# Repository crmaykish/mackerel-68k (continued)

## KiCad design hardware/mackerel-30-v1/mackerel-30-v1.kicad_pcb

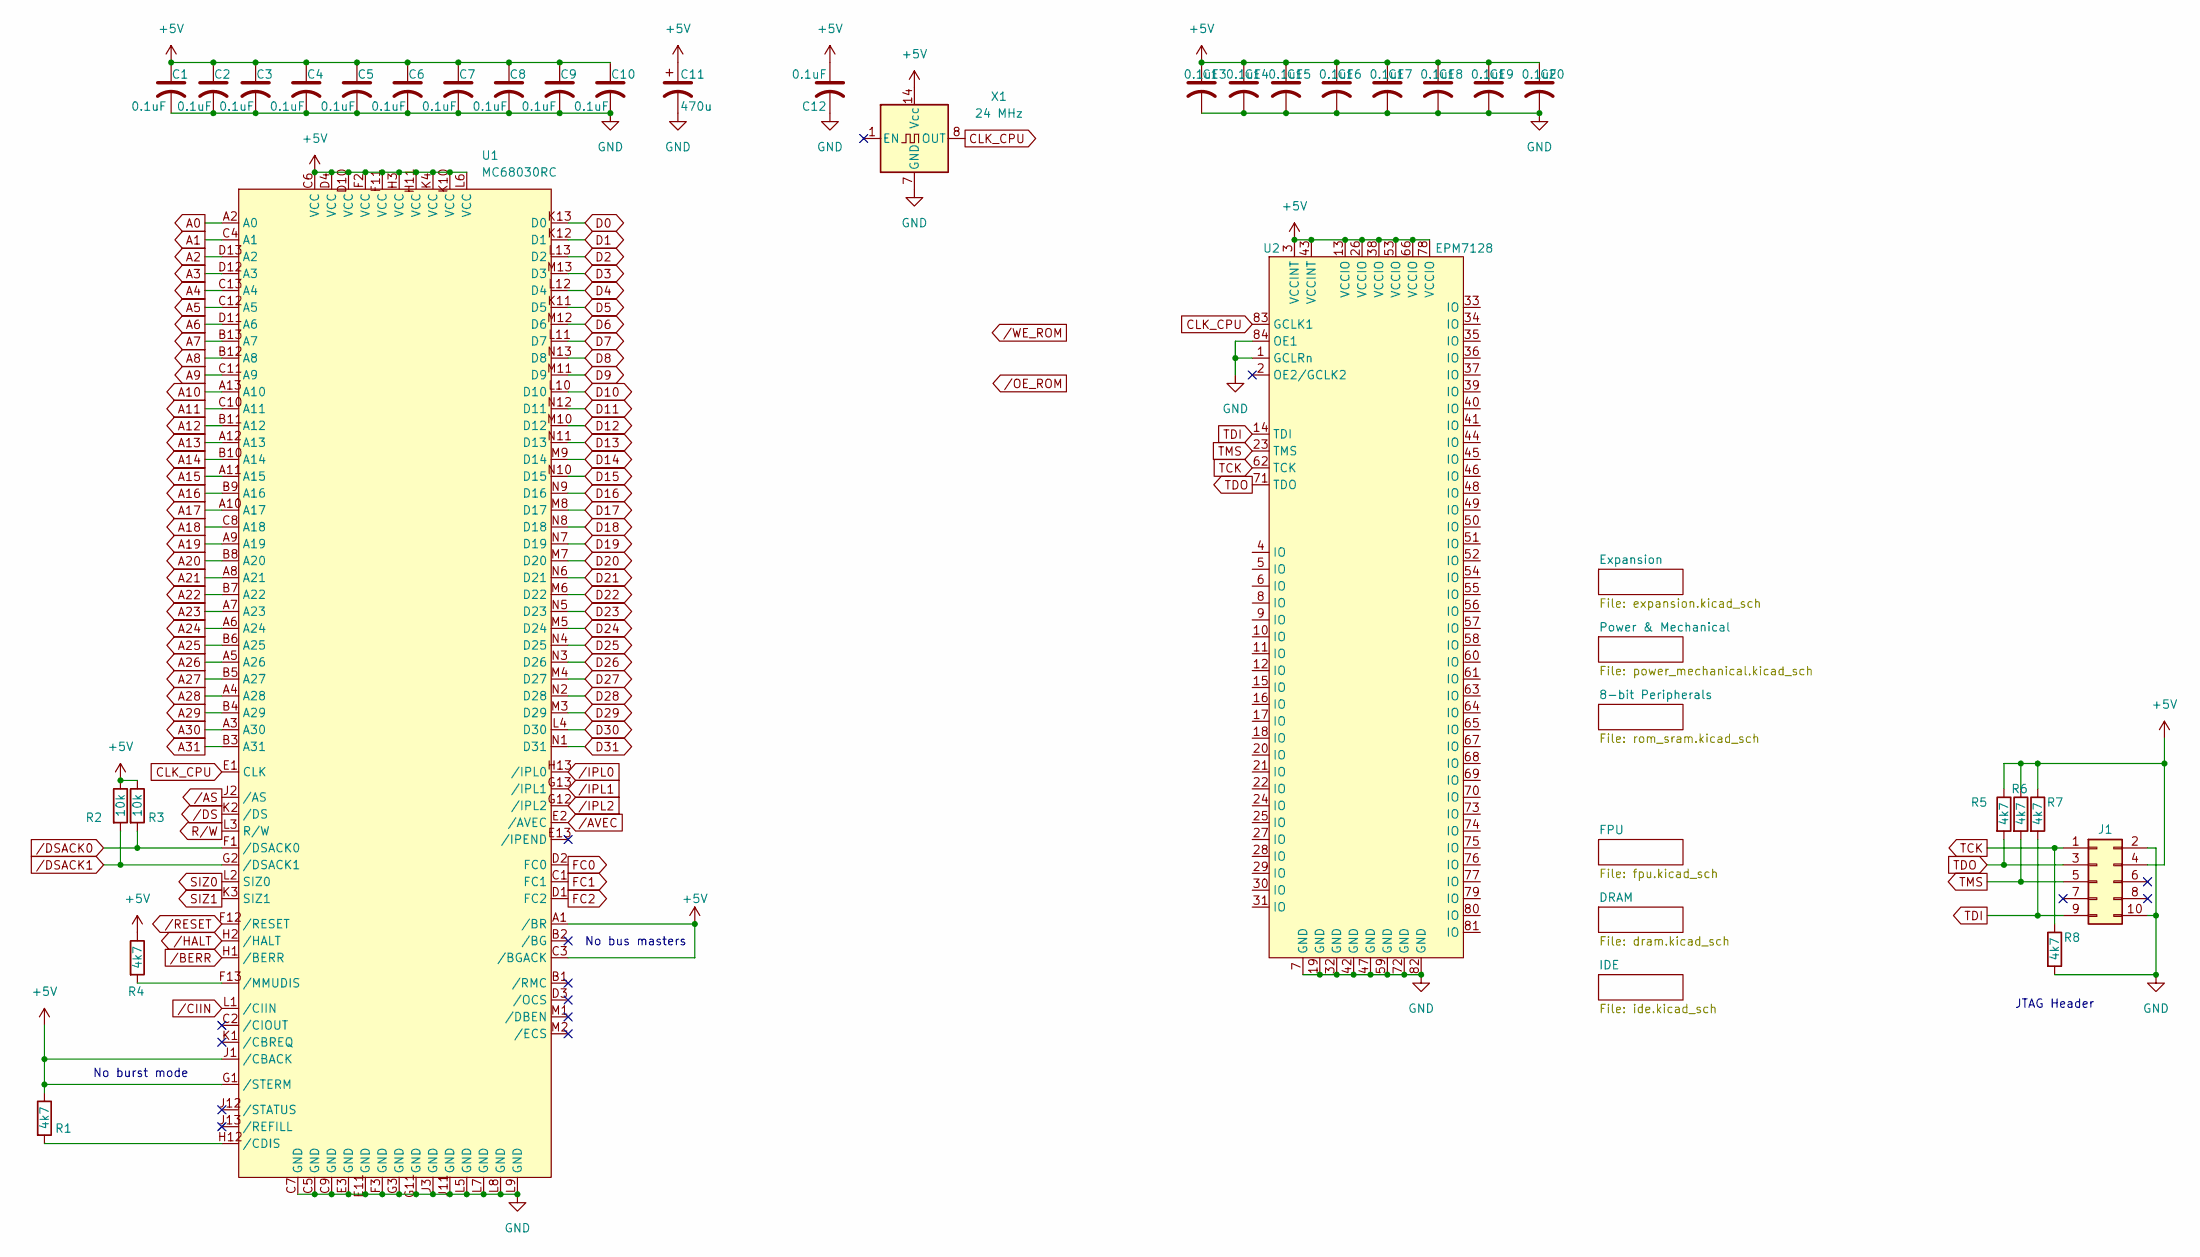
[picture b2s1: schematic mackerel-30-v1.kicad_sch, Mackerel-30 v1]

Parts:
C1, C2, C3, C4, C5, C6, C7, C8, C9, C10, C12, C13, C14, C15, C16, C17, C18, C19, C20: 0.1uF; C_1206_3216Metric_Pad1.33x1.80mm_HandSolder
C11: 470u; CP_Radial_D8.0mm_P3.50mm
J1: Conn_02x05_Odd_Even; IDC-Header_2x05_P2.54mm_Vertical
R1, R4, R5, R6, R7, R8: 4k7; R_1206_3216Metric_Pad1.30x1.75mm_HandSolder
R2, R3: 10k; R_1206_3216Metric_Pad1.30x1.75mm_HandSolder
U1: MC68030RC; PGA169
U2: EPM7128; PLCC-84_THT-Socket
X1: 24 MHz; Oscillator_DIP-14

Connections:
+5V: C1.1, C2.1, C3.1, C4.1, C5.1, C6.1, C7.1, C8.1, C9.1, C10.1, C11.1, C12.1, C13.1, C14.1, C15.1, C16.1, C17.1, C18.1, C19.1, C20.1, J1.4, R1.1, R2.1, R3.1, R4.1, R5.1, R6.1, R7.1, U1.A1 (/BR), U1.C3 (/BGACK), U1.C6 (VCC), U1.D4 (VCC), U1.D10 (VCC), U1.F2 (VCC), U1.F11 (VCC), U1.G1 (/STERM), U1.H3 (VCC), U1.H11 (VCC), U1.J1 (/CBACK), U1.K4 (VCC), U1.K10 (VCC), U1.L6 (VCC), U2.3 (VCCINT), U2.13 (VCCIO), U2.26 (VCCIO), U2.38 (VCCIO), U2.43 (VCCINT), U2.53 (VCCIO), U2.66 (VCCIO), U2.78 (VCCIO), X1.14 (Vcc); also elsewhere on the board
A0: U1.A2 (A0); also elsewhere on the board
A1: U1.C4 (A1); also elsewhere on the board
A2: U1.D13 (A2); also elsewhere on the board
A3: U1.D12 (A3); also elsewhere on the board
A4: U1.C13 (A4); also elsewhere on the board
A5: U1.C12 (A5); also elsewhere on the board
A6: U1.D11 (A6); also elsewhere on the board
A7: U1.B13 (A7); also elsewhere on the board
A8: U1.B12 (A8); also elsewhere on the board
A9: U1.C11 (A9); also elsewhere on the board
A10: U1.A13 (A10); also elsewhere on the board
A11: U1.C10 (A11); also elsewhere on the board
A12: U1.B11 (A12); also elsewhere on the board
A13: U1.A12 (A13); also elsewhere on the board
A14: U1.B10 (A14); also elsewhere on the board
A15: U1.A11 (A15); also elsewhere on the board
A16: U1.B9 (A16); also elsewhere on the board
A17: U1.A10 (A17); also elsewhere on the board
A18: U1.C8 (A18); also elsewhere on the board
A19: U1.A9 (A19); also elsewhere on the board
A20: U1.B8 (A20); also elsewhere on the board
A21: U1.A8 (A21); also elsewhere on the board
A22: U1.B7 (A22); also elsewhere on the board
A23: U1.A7 (A23); also elsewhere on the board
A24: U1.A6 (A24)
A25: U1.B6 (A25)
A26: U1.A5 (A26)
A27: U1.B5 (A27)
A28: U1.A4 (A28)
A29: U1.B4 (A29)
A30: U1.A3 (A30)
A31: U1.B3 (A31)
CLK_CPU: U1.E1 (CLK), U2.83 (GCLK1), X1.8 (OUT); also elsewhere on the board
D0: U1.K13 (D0); also elsewhere on the board
D1: U1.K12 (D1); also elsewhere on the board
D2: U1.L13 (D2); also elsewhere on the board
D3: U1.M13 (D3); also elsewhere on the board
D4: U1.L12 (D4); also elsewhere on the board
D5: U1.K11 (D5); also elsewhere on the board
D6: U1.M12 (D6); also elsewhere on the board
D7: U1.L11 (D7); also elsewhere on the board
D8: U1.N13 (D8); also elsewhere on the board
D9: U1.M11 (D9); also elsewhere on the board
D10: U1.L10 (D10); also elsewhere on the board
D11: U1.N12 (D11); also elsewhere on the board
D12: U1.M10 (D12); also elsewhere on the board
D13: U1.N11 (D13); also elsewhere on the board
D14: U1.M9 (D14); also elsewhere on the board
D15: U1.N10 (D15); also elsewhere on the board
D16: U1.N9 (D16); also elsewhere on the board
D17: U1.M8 (D17); also elsewhere on the board
D18: U1.N8 (D18); also elsewhere on the board
D19: U1.N7 (D19); also elsewhere on the board
D20: U1.M7 (D20); also elsewhere on the board
D21: U1.N6 (D21); also elsewhere on the board
D22: U1.M6 (D22); also elsewhere on the board
D23: U1.N5 (D23); also elsewhere on the board
D24: U1.M5 (D24); also elsewhere on the board
D25: U1.N4 (D25); also elsewhere on the board
D26: U1.N3 (D26); also elsewhere on the board
D27: U1.M4 (D27); also elsewhere on the board
D28: U1.N2 (D28); also elsewhere on the board
D29: U1.M3 (D29); also elsewhere on the board
D30: U1.L4 (D30); also elsewhere on the board
D31: U1.N1 (D31); also elsewhere on the board
FC0: U1.D2 (FC0)
FC1: U1.C1 (FC1)
FC2: U1.D1 (FC2)
GND: C1.2, C2.2, C3.2, C4.2, C5.2, C6.2, C7.2, C8.2, C9.2, C10.2, C11.2, C12.2, C13.2, C14.2, C15.2, C16.2, C17.2, C18.2, C19.2, C20.2, J1.2, J1.10, R8.2, U1.C5 (GND), U1.C7 (GND), U1.C9 (GND), U1.E3 (GND), U1.E11 (GND), U1.F3 (GND), U1.G3 (GND), U1.G11 (GND), U1.J3 (GND), U1.J11 (GND), U1.L5 (GND), U1.L7 (GND), U1.L8 (GND), U1.L9 (GND), U2.1 (GCLRn), U2.7 (GND), U2.19 (GND), U2.32 (GND), U2.42 (GND), U2.47 (GND), U2.59 (GND), U2.72 (GND), U2.82 (GND), U2.84 (OE1), X1.7 (GND); also elsewhere on the board
unnamed: R1.2, U1.H12 (/CDIS)
unnamed: R4.2, U1.F13 (/MMUDIS)
R/W: U1.L3 (R/W); also elsewhere on the board
SIZ0: U1.L2 (SIZ0)
SIZ1: U1.K3 (SIZ1)
TCK: J1.1, R8.1, U2.62 (TCK)
TDI: J1.9, R7.2, U2.14 (TDI)
TDO: J1.3, R5.2, U2.71 (TDO)
TMS: J1.5, R6.2, U2.23 (TMS)
/AS: U1.J2 (/AS); also elsewhere on the board
/AVEC: U1.E2 (/AVEC)
/BERR: U1.H1 (/BERR)
/CIIN: U1.L1 (/CIIN)
/DS: U1.K2 (/DS); also elsewhere on the board
/DSACK0: R3.2, U1.F1 (/DSACK0); also elsewhere on the board
/DSACK1: R2.2, U1.G2 (/DSACK1); also elsewhere on the board
/HALT: U1.H2 (/HALT)
/IPL0: U1.H13 (/IPL0)
/IPL1: U1.G13 (/IPL1)
/IPL2: U1.G12 (/IPL2)
/RESET: U1.F12 (/RESET); also elsewhere on the board

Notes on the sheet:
No burst mode
JTAG Header
No bus masters

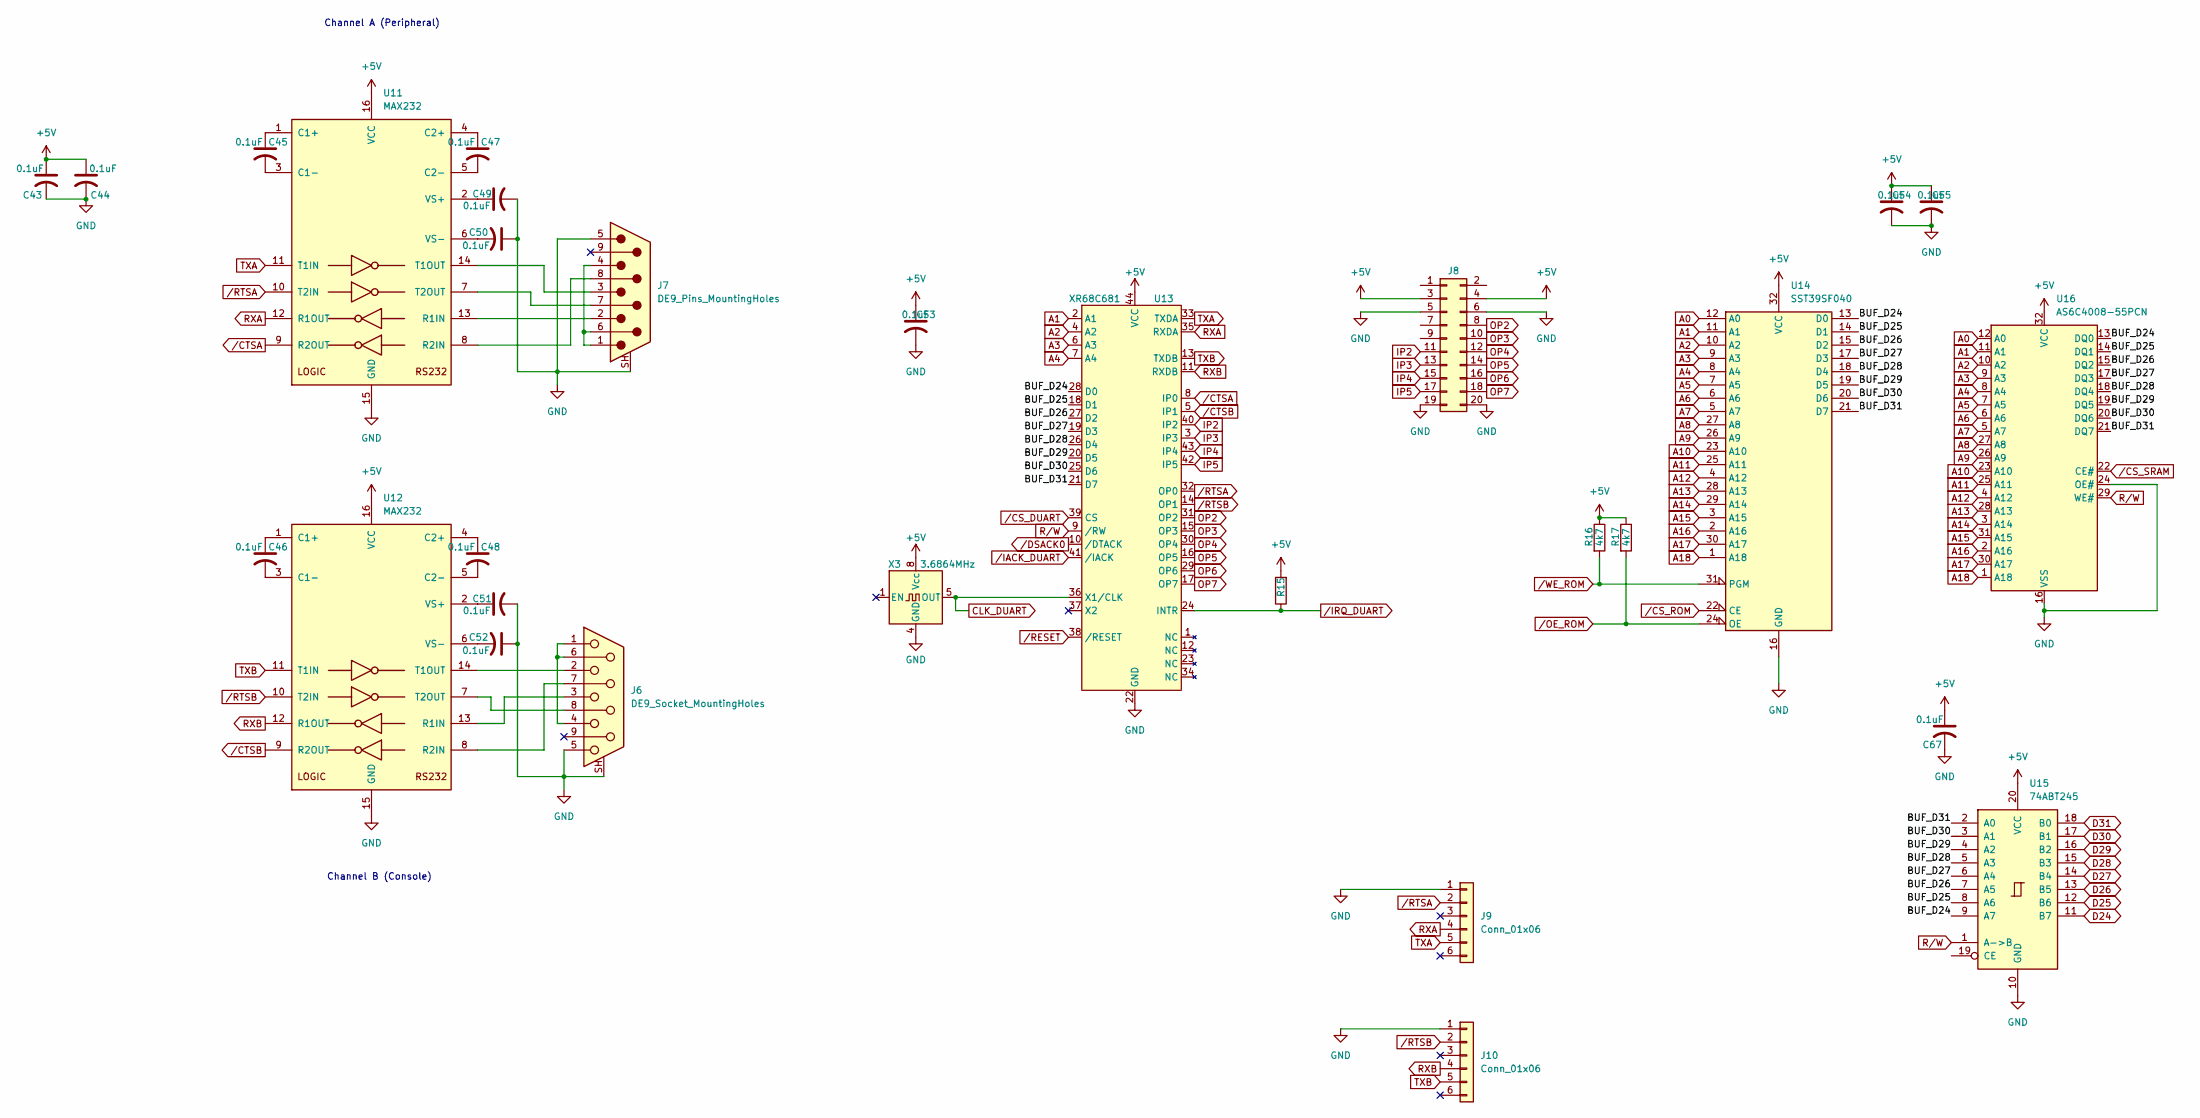
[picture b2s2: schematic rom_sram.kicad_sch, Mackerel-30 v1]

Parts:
C43, C44, C45, C46, C47, C48, C49, C50, C51, C52, C53, C54, C55, C67: 0.1uF; C_1206_3216Metric_Pad1.33x1.80mm_HandSolder
J6: DE9_Socket_MountingHoles; DSUB-9_Socket_Horizontal_P2.77x2.84mm_EdgePinOffset7.70mm_H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
J7: DE9_Pins_MountingHoles; DSUB-9_Pins_Horizontal_P2.77x2.84mm_EdgePinOffset7.70mm_Hou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
J8: Conn_02x10_Odd_Even; PinHeader_2x10_P2.54mm_Vertical
J9, J10: Conn_01x06; PinHeader_1x06_P2.54mm_Vertical
R15, R16, R17: 4k7; R_1206_3216Metric_Pad1.30x1.75mm_HandSolder
U11, U12: MAX232; DIP-16_W7.62mm_Socket
U13: XR68C681; PLCC-44_THT-Socket
U14: SST39SF040; DIP-32_W15.24mm_Socket
U15: 74ABT245; DIP-20_W7.62mm_Socket_LongPads
U16: AS6C4008-55PCN; DIP-32_W15.24mm_Socket
X3: 3.6864MHz; Oscillator_DIP-8

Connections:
+5V: C43.1, C44.1, C53.1, C54.1, C55.1, C67.1, J8.3, J8.4, R15.2, R16.1, R17.1, U11.16 (VCC), U12.16 (VCC), U13.44 (VCC), U14.32 (VCC), U15.20 (VCC), U16.32 (VCC), X3.8 (Vcc); also elsewhere on the board
/8-bit Peripherals/BUF_D24: U13.28 (D0), U14.13 (D0), U15.9 (A7), U16.13 (DQ0)
/8-bit Peripherals/BUF_D25: U13.18 (D1), U14.14 (D1), U15.8 (A6), U16.14 (DQ1)
/8-bit Peripherals/BUF_D26: U13.27 (D2), U14.15 (D2), U15.7 (A5), U16.15 (DQ2)
/8-bit Peripherals/BUF_D27: U13.19 (D3), U14.17 (D3), U15.6 (A4), U16.17 (DQ3)
/8-bit Peripherals/BUF_D28: U13.26 (D4), U14.18 (D4), U15.5 (A3), U16.18 (DQ4)
/8-bit Peripherals/BUF_D29: U13.20 (D5), U14.19 (D5), U15.4 (A2), U16.19 (DQ5)
/8-bit Peripherals/BUF_D30: U13.25 (D6), U14.20 (D6), U15.3 (A1), U16.20 (DQ6)
/8-bit Peripherals/BUF_D31: U13.21 (D7), U14.21 (D7), U15.2 (A0), U16.21 (DQ7)
A0: U14.12 (A0), U16.12 (A0); also elsewhere on the board
A1: U13.2 (A1), U14.11 (A1), U16.11 (A1); also elsewhere on the board
A2: U13.4 (A2), U14.10 (A2), U16.10 (A2); also elsewhere on the board
A3: U13.6 (A3), U14.9 (A3), U16.9 (A3); also elsewhere on the board
A4: U13.7 (A4), U14.8 (A4), U16.8 (A4); also elsewhere on the board
A5: U14.7 (A5), U16.7 (A5); also elsewhere on the board
A6: U14.6 (A6), U16.6 (A6); also elsewhere on the board
A7: U14.5 (A7), U16.5 (A7); also elsewhere on the board
A8: U14.27 (A8), U16.27 (A8); also elsewhere on the board
A9: U14.26 (A9), U16.26 (A9); also elsewhere on the board
A10: U14.23 (A10), U16.23 (A10); also elsewhere on the board
A11: U14.25 (A11), U16.25 (A11); also elsewhere on the board
A12: U14.4 (A12), U16.4 (A12); also elsewhere on the board
A13: U14.28 (A13), U16.28 (A13); also elsewhere on the board
A14: U14.29 (A14), U16.3 (A14); also elsewhere on the board
A15: U14.3 (A15), U16.31 (A15); also elsewhere on the board
A16: U14.2 (A16), U16.2 (A16); also elsewhere on the board
A17: U14.30 (A17), U16.30 (A17); also elsewhere on the board
A18: U14.1 (A18), U16.1 (A18); also elsewhere on the board
CLK_DUART: U13.36 (X1/CLK), X3.5 (OUT)
D24: U15.11 (B7); also elsewhere on the board
D25: U15.12 (B6); also elsewhere on the board
D26: U15.13 (B5); also elsewhere on the board
D27: U15.14 (B4); also elsewhere on the board
D28: U15.15 (B3); also elsewhere on the board
D29: U15.16 (B2); also elsewhere on the board
D30: U15.17 (B1); also elsewhere on the board
D31: U15.18 (B0); also elsewhere on the board
GND: C43.2, C44.2, C49.2, C50.1, C51.2, C52.1, C53.2, C54.2, C55.2, C67.2, J6.5, J6.SH (PAD), J7.5, J7.SH (PAD), J8.5, J8.6, J8.19, J8.20, J9.1, J10.1, U11.15 (GND), U12.15 (GND), U13.22 (GND), U14.16 (GND), U15.10 (GND), U16.16 (VSS), U16.24 (OE#), X3.4 (GND); also elsewhere on the board
IP2: J8.11, U13.40 (IP2)
IP3: J8.13, U13.3 (IP3)
IP4: J8.15, U13.43 (IP4)
IP5: J8.17, U13.42 (IP5)
unnamed: J6.1, J6.4, J6.6
unnamed: J7.1, J7.4, J7.6
unnamed: C45.1, U11.1 (C1+)
unnamed: C45.2, U11.3 (C1-)
unnamed: C47.1, U11.4 (C2+)
unnamed: C47.2, U11.5 (C2-)
unnamed: J7.2, U11.13 (R1IN)
unnamed: J7.8, U11.8 (R2IN)
unnamed: J7.3, U11.14 (T1OUT)
unnamed: J7.7, U11.7 (T2OUT)
unnamed: C49.1, U11.2 (VS+)
unnamed: C50.2, U11.6 (VS-)
unnamed: C46.1, U12.1 (C1+)
unnamed: C46.2, U12.3 (C1-)
unnamed: C48.1, U12.4 (C2+)
unnamed: C48.2, U12.5 (C2-)
unnamed: J6.3, U12.13 (R1IN)
unnamed: J6.7, U12.8 (R2IN)
unnamed: J6.2, U12.14 (T1OUT)
unnamed: J6.8, U12.7 (T2OUT)
unnamed: C51.1, U12.2 (VS+)
unnamed: C52.2, U12.6 (VS-)
OP2: J8.8, U13.31 (OP2)
OP3: J8.10, U13.15 (OP3)
OP4: J8.12, U13.30 (OP4)
OP5: J8.14, U13.16 (OP5)
OP6: J8.16, U13.29 (OP6)
OP7: J8.18, U13.17 (OP7)
RXA: J9.4, U11.12 (R1OUT), U13.35 (RXDA)
RXB: J10.4, U12.12 (R1OUT), U13.11 (RXDB)
R/W: U13.9 (/RW), U15.1 (A->B), U16.29 (WE#); also elsewhere on the board
TXA: J9.5, U11.11 (T1IN), U13.33 (TXDA)
TXB: J10.5, U12.11 (T1IN), U13.13 (TXDB)
/CS_DUART: U13.39 (CS)
/CS_ROM: U14.22 (CE)
/CS_SRAM: U16.22 (CE#)
/CTSA: U11.9 (R2OUT), U13.8 (IP0)
/CTSB: U12.9 (R2OUT), U13.5 (IP1)
/DSACK0: U13.10 (/DTACK); also elsewhere on the board
/IACK_DUART: U13.41 (/IACK)
/IRQ_DUART: R15.1, U13.24 (INTR)
/OE_ROM: R17.2, U14.24 (OE)
/RESET: U13.38 (/RESET); also elsewhere on the board
/RTSA: J9.2, U11.10 (T2IN), U13.32 (OP0)
/RTSB: J10.2, U12.10 (T2IN), U13.14 (OP1)
/WE_ROM: R16.2, U14.31 (PGM)

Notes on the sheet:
Channel A (Peripheral)
Channel B (Console)

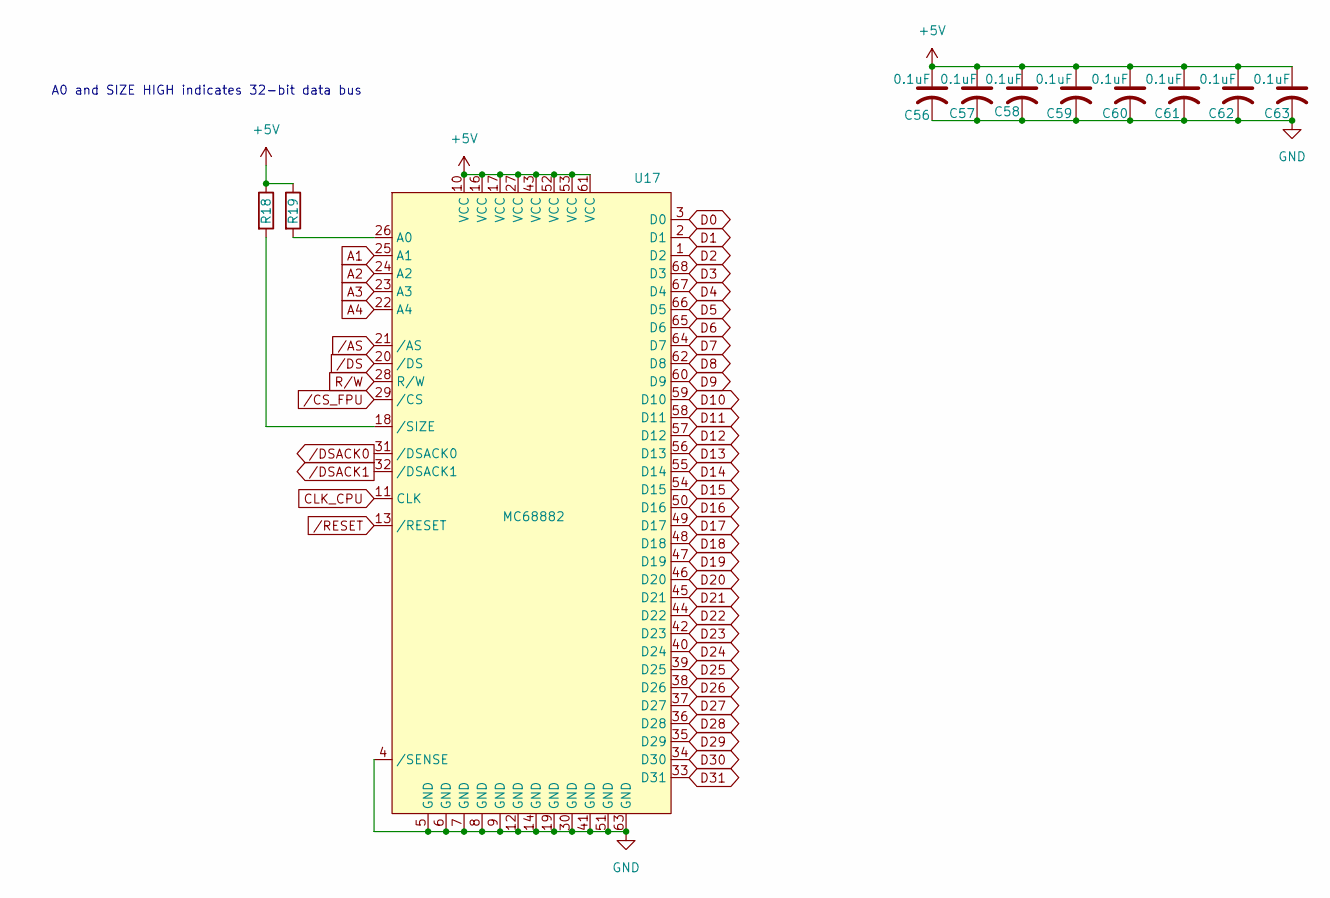
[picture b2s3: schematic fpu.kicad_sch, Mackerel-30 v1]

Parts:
C56, C57, C58, C59, C60, C61, C62, C63: 0.1uF; C_1206_3216Metric_Pad1.33x1.80mm_HandSolder
R18, R19: 4k7; R_1206_3216Metric_Pad1.30x1.75mm_HandSolder
U17: MC68882; PLCC-68_THT-Socket

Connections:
+5V: C56.1, C57.1, C58.1, C59.1, C60.1, C61.1, C62.1, C63.1, R18.1, R19.1, U17.10 (VCC), U17.16 (VCC), U17.17 (VCC), U17.27 (VCC), U17.43 (VCC), U17.52 (VCC), U17.53 (VCC), U17.61 (VCC); also elsewhere on the board
A1: U17.25 (A1); also elsewhere on the board
A2: U17.24 (A2); also elsewhere on the board
A3: U17.23 (A3); also elsewhere on the board
A4: U17.22 (A4); also elsewhere on the board
CLK_CPU: U17.11 (CLK); also elsewhere on the board
D0: U17.3 (D0); also elsewhere on the board
D1: U17.2 (D1); also elsewhere on the board
D2: U17.1 (D2); also elsewhere on the board
D3: U17.68 (D3); also elsewhere on the board
D4: U17.67 (D4); also elsewhere on the board
D5: U17.66 (D5); also elsewhere on the board
D6: U17.65 (D6); also elsewhere on the board
D7: U17.64 (D7); also elsewhere on the board
D8: U17.62 (D8); also elsewhere on the board
D9: U17.60 (D9); also elsewhere on the board
D10: U17.59 (D10); also elsewhere on the board
D11: U17.58 (D11); also elsewhere on the board
D12: U17.57 (D12); also elsewhere on the board
D13: U17.56 (D13); also elsewhere on the board
D14: U17.55 (D14); also elsewhere on the board
D15: U17.54 (D15); also elsewhere on the board
D16: U17.50 (D16); also elsewhere on the board
D17: U17.49 (D17); also elsewhere on the board
D18: U17.48 (D18); also elsewhere on the board
D19: U17.47 (D19); also elsewhere on the board
D20: U17.46 (D20); also elsewhere on the board
D21: U17.45 (D21); also elsewhere on the board
D22: U17.44 (D22); also elsewhere on the board
D23: U17.42 (D23); also elsewhere on the board
D24: U17.40 (D24); also elsewhere on the board
D25: U17.39 (D25); also elsewhere on the board
D26: U17.38 (D26); also elsewhere on the board
D27: U17.37 (D27); also elsewhere on the board
D28: U17.36 (D28); also elsewhere on the board
D29: U17.35 (D29); also elsewhere on the board
D30: U17.34 (D30); also elsewhere on the board
D31: U17.33 (D31); also elsewhere on the board
GND: C56.2, C57.2, C58.2, C59.2, C60.2, C61.2, C62.2, C63.2, U17.4 (/SENSE), U17.5 (GND), U17.6 (GND), U17.7 (GND), U17.8 (GND), U17.9 (GND), U17.12 (GND), U17.14 (GND), U17.19 (GND), U17.30 (GND), U17.41 (GND), U17.51 (GND), U17.63 (GND); also elsewhere on the board
unnamed: R19.2, U17.26 (A0)
unnamed: R18.2, U17.18 (/SIZE)
R/W: U17.28 (R/W); also elsewhere on the board
/AS: U17.21 (/AS); also elsewhere on the board
/CS_FPU: U17.29 (/CS)
/DS: U17.20 (/DS); also elsewhere on the board
/DSACK0: U17.31 (/DSACK0); also elsewhere on the board
/DSACK1: U17.32 (/DSACK1); also elsewhere on the board
/RESET: U17.13 (/RESET); also elsewhere on the board

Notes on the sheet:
A0 and SIZE HIGH indicates 32-bit data bus

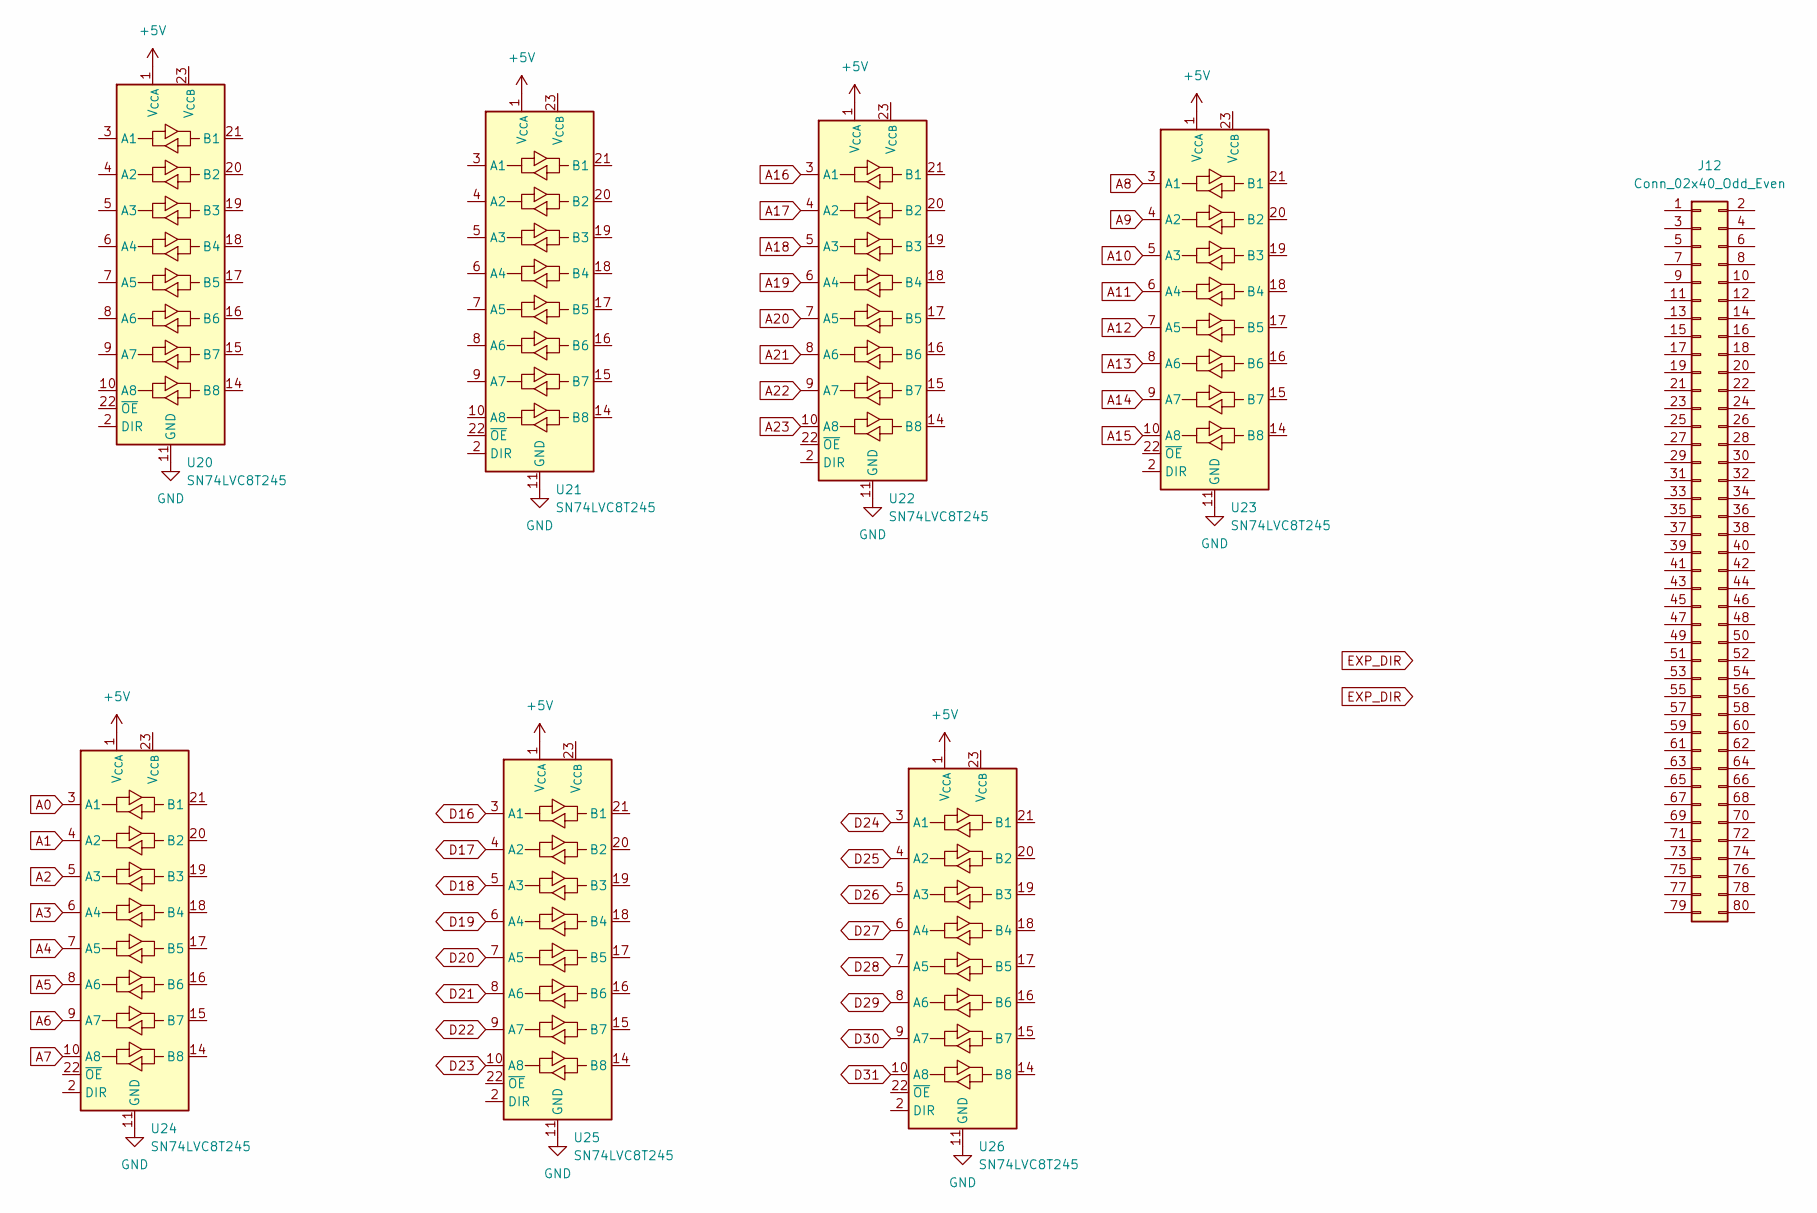
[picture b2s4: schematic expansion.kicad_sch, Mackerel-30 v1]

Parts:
J12: Conn_02x40_Odd_Even; PinSocket_2x40_P2.54mm_Vertical
U20, U21, U22, U23, U24, U25, U26: SN74LVC8T245; SOIC-24W_7.5x15.4mm_P1.27mm

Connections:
+5V: U20.1 (V_{CCA}), U21.1 (V_{CCA}), U22.1 (V_{CCA}), U23.1 (V_{CCA}), U24.1 (V_{CCA}), U25.1 (V_{CCA}), U26.1 (V_{CCA}); also elsewhere on the board
A0: U24.3 (A1); also elsewhere on the board
A1: U24.4 (A2); also elsewhere on the board
A2: U24.5 (A3); also elsewhere on the board
A3: U24.6 (A4); also elsewhere on the board
A4: U24.7 (A5); also elsewhere on the board
A5: U24.8 (A6); also elsewhere on the board
A6: U24.9 (A7); also elsewhere on the board
A7: U24.10 (A8); also elsewhere on the board
A8: U23.3 (A1); also elsewhere on the board
A9: U23.4 (A2); also elsewhere on the board
A10: U23.5 (A3); also elsewhere on the board
A11: U23.6 (A4); also elsewhere on the board
A12: U23.7 (A5); also elsewhere on the board
A13: U23.8 (A6); also elsewhere on the board
A14: U23.9 (A7); also elsewhere on the board
A15: U23.10 (A8); also elsewhere on the board
A16: U22.3 (A1); also elsewhere on the board
A17: U22.4 (A2); also elsewhere on the board
A18: U22.5 (A3); also elsewhere on the board
A19: U22.6 (A4); also elsewhere on the board
A20: U22.7 (A5); also elsewhere on the board
A21: U22.8 (A6); also elsewhere on the board
A22: U22.9 (A7); also elsewhere on the board
A23: U22.10 (A8); also elsewhere on the board
D16: U25.3 (A1); also elsewhere on the board
D17: U25.4 (A2); also elsewhere on the board
D18: U25.5 (A3); also elsewhere on the board
D19: U25.6 (A4); also elsewhere on the board
D20: U25.7 (A5); also elsewhere on the board
D21: U25.8 (A6); also elsewhere on the board
D22: U25.9 (A7); also elsewhere on the board
D23: U25.10 (A8); also elsewhere on the board
D24: U26.3 (A1); also elsewhere on the board
D25: U26.4 (A2); also elsewhere on the board
D26: U26.5 (A3); also elsewhere on the board
D27: U26.6 (A4); also elsewhere on the board
D28: U26.7 (A5); also elsewhere on the board
D29: U26.8 (A6); also elsewhere on the board
D30: U26.9 (A7); also elsewhere on the board
D31: U26.10 (A8); also elsewhere on the board
GND: U20.11 (GND), U20.12 (GND), U20.13 (GND), U21.11 (GND), U21.12 (GND), U21.13 (GND), U22.11 (GND), U22.12 (GND), U22.13 (GND), U23.11 (GND), U23.12 (GND), U23.13 (GND), U24.11 (GND), U24.12 (GND), U24.13 (GND), U25.11 (GND), U25.12 (GND), U25.13 (GND), U26.11 (GND), U26.12 (GND), U26.13 (GND); also elsewhere on the board
unnamed: U20.23 (V_{CCB}), U20.24 (V_{CCB})
unnamed: U21.23 (V_{CCB}), U21.24 (V_{CCB})
unnamed: U22.23 (V_{CCB}), U22.24 (V_{CCB})
unnamed: U23.23 (V_{CCB}), U23.24 (V_{CCB})
unnamed: U24.23 (V_{CCB}), U24.24 (V_{CCB})
unnamed: U25.23 (V_{CCB}), U25.24 (V_{CCB})
unnamed: U26.23 (V_{CCB}), U26.24 (V_{CCB})

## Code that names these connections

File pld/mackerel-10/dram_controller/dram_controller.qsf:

# -------------------------------------------------------------------------- #
#
# Copyright (C) 1991-2013 Altera Corporation
# Your use of Altera Corporation's design tools, logic functions 
# and other software and tools, and its AMPP partner logic 
# functions, and any output files from any of the foregoing 
# (including device programming or simulation files), and any 
# associated documentation or information are expressly subject 
# to the terms and conditions of the Altera Program License 
# Subscription Agreement, Altera MegaCore Function License 
# Agreement, or other applicable license agreement, including, 
# without limitation, that your use is for the sole purpose of 
# programming logic devices manufactured by Altera and sold by 
# Altera or its authorized distributors.  Please refer to the 
# applicable agreement for further details.
#
# -------------------------------------------------------------------------- #
#
# Quartus II 64-Bit
# Version 13.0.1 Build 232 06/12/2013 Service Pack 1 SJ Web Edition
# Date created = 18:38:20  September 02, 2024
#
# -------------------------------------------------------------------------- #
#
# Notes:
#
# 1) The default values for assignments are stored in the file:
#		dram_controller_assignment_defaults.qdf
#    If this file doesn't exist, see file:
#		assignment_defaults.qdf
#
# 2) Altera recommends that you do not modify this file. This
#    file is updated automatically by the Quartus II software
#    and any changes you make may be lost or overwritten.
#
# -------------------------------------------------------------------------- #


set_global_assignment -name FAMILY MAX7000S
set_global_assignment -name DEVICE "EPM7128SLC84-15"
set_global_assignment -name TOP_LEVEL_ENTITY dram_controller
set_global_assignment -name ORIGINAL_QUARTUS_VERSION "13.0 SP1"
set_global_assignment -name PROJECT_CREATION_TIME_DATE "18:38:20  SEPTEMBER 02, 2024"
set_global_assignment -name LAST_QUARTUS_VERSION "13.0 SP1"
set_global_assignment -name PROJECT_OUTPUT_DIRECTORY output_files
set_global_assignment -name DEVICE_FILTER_PIN_COUNT 84
set_global_assignment -name DEVICE_FILTER_SPEED_GRADE 15
set_global_assignment -name ERROR_CHECK_FREQUENCY_DIVISOR "-1"
set_global_assignment -name MIN_CORE_JUNCTION_TEMP 0
set_global_assignment -name MAX_CORE_JUNCTION_TEMP 85
set_global_assignment -name VERILOG_FILE dram_controller.v
set_global_assignment -name EDA_SIMULATION_TOOL "ModelSim-Altera (Verilog)"
set_global_assignment -name EDA_OUTPUT_DATA_FORMAT "VERILOG HDL" -section_id eda_simulation
set_global_assignment -name EDA_TIME_SCALE "1 ps" -section_id eda_simulation
set_global_assignment -name MAX7000_DEVICE_IO_STANDARD TTL

set_location_assignment PIN_74 -to ADDR_IN[23]
set_location_assignment PIN_73 -to ADDR_IN[22]
set_location_assignment PIN_70 -to ADDR_IN[21]
set_location_assignment PIN_69 -to ADDR_IN[20]
set_location_assignment PIN_68 -to ADDR_IN[19]
set_location_assignment PIN_67 -to ADDR_IN[18]
set_location_assignment PIN_65 -to ADDR_IN[17]
set_location_assignment PIN_64 -to ADDR_IN[16]
set_location_assignment PIN_63 -to ADDR_IN[15]
set_location_assignment PIN_61 -to ADDR_IN[14]
set_location_assignment PIN_60 -to ADDR_IN[13]
set_location_assignment PIN_58 -to ADDR_IN[12]
set_location_assignment PIN_57 -to ADDR_IN[11]
set_location_assignment PIN_56 -to ADDR_IN[10]
set_location_assignment PIN_55 -to ADDR_IN[9]
set_location_assignment PIN_54 -to ADDR_IN[8]
set_location_assignment PIN_52 -to ADDR_IN[7]
set_location_assignment PIN_51 -to ADDR_IN[6]
set_location_assignment PIN_50 -to ADDR_IN[5]
set_location_assignment PIN_49 -to ADDR_IN[4]
set_location_assignment PIN_48 -to ADDR_IN[3]
set_location_assignment PIN_46 -to ADDR_IN[2]
set_location_assignment PIN_45 -to ADDR_IN[1]
set_location_assignment PIN_44 -to AS
set_location_assignment PIN_41 -to UDS
set_location_assignment PIN_40 -to LDS
set_location_assignment PIN_39 -to RW
set_location_assignment PIN_25 -to DTACK_DRAM
set_location_assignment PIN_24 -to CS
set_location_assignment PIN_4 -to ADDR_OUT[10]
set_location_assignment PIN_5 -to ADDR_OUT[9]
set_location_assignment PIN_6 -to ADDR_OUT[8]
set_location_assignment PIN_8 -to ADDR_OUT[7]
set_location_assignment PIN_9 -to ADDR_OUT[6]
set_location_assignment PIN_10 -to ADDR_OUT[5]
set_location_assignment PIN_11 -to ADDR_OUT[4]
set_location_assignment PIN_12 -to ADDR_OUT[3]
set_location_assignment PIN_15 -to ADDR_OUT[2]
set_location_assignment PIN_16 -to ADDR_OUT[1]
set_location_assignment PIN_17 -to ADDR_OUT[0]
set_location_assignment PIN_18 -to CASB0
set_location_assignment PIN_20 -to CASA0
set_location_assignment PIN_21 -to CASA1
set_location_assignment PIN_22 -to CASB1
set_location_assignment PIN_83 -to CLK
set_location_assignment PIN_2 -to CLK_ALT
set_location_assignment PIN_75 -to RASA
set_location_assignment PIN_77 -to RASB
set_location_assignment PIN_76 -to RST
set_location_assignment PIN_80 -to WRA
set_location_assignment PIN_81 -to WRB
set_location_assignment PIN_79 -to ADDR_OUT_11

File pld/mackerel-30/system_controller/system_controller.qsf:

# -------------------------------------------------------------------------- #
#
# Copyright (C) 1991-2013 Altera Corporation
# Your use of Altera Corporation's design tools, logic functions 
# and other software and tools, and its AMPP partner logic 
# functions, and any output files from any of the foregoing 
# (including device programming or simulation files), and any 
# associated documentation or information are expressly subject 
# to the terms and conditions of the Altera Program License 
# Subscription Agreement, Altera MegaCore Function License 
# Agreement, or other applicable license agreement, including, 
# without limitation, that your use is for the sole purpose of 
# programming logic devices manufactured by Altera and sold by 
# Altera or its authorized distributors.  Please refer to the 
# applicable agreement for further details.
#
# -------------------------------------------------------------------------- #
#
# Quartus II 64-Bit
# Version 13.0.1 Build 232 06/12/2013 Service Pack 1 SJ Web Edition
# Date created = 19:01:53  November 22, 2024
#
# -------------------------------------------------------------------------- #
#
# Notes:
#
# 1) The default values for assignments are stored in the file:
#		system_controller_assignment_defaults.qdf
#    If this file doesn't exist, see file:
#		assignment_defaults.qdf
#
# 2) Altera recommends that you do not modify this file. This
#    file is updated automatically by the Quartus II software
#    and any changes you make may be lost or overwritten.
#
# -------------------------------------------------------------------------- #


set_global_assignment -name FAMILY MAX7000S
set_global_assignment -name DEVICE "EPM7128SLC84-15"
set_global_assignment -name TOP_LEVEL_ENTITY system_controller
set_global_assignment -name ORIGINAL_QUARTUS_VERSION "13.0 SP1"
set_global_assignment -name PROJECT_CREATION_TIME_DATE "19:01:53  NOVEMBER 22, 2024"
set_global_assignment -name LAST_QUARTUS_VERSION "13.0 SP1"
set_global_assignment -name PROJECT_OUTPUT_DIRECTORY output_files
set_global_assignment -name DEVICE_FILTER_PIN_COUNT 84
set_global_assignment -name DEVICE_FILTER_SPEED_GRADE 15
set_global_assignment -name ERROR_CHECK_FREQUENCY_DIVISOR "-1"
set_global_assignment -name MIN_CORE_JUNCTION_TEMP 0
set_global_assignment -name MAX_CORE_JUNCTION_TEMP 85
set_global_assignment -name MAX7000_DEVICE_IO_STANDARD TTL
set_location_assignment PIN_67 -to AH[31]
set_location_assignment PIN_69 -to AH[30]
set_location_assignment PIN_68 -to AH[29]
set_location_assignment PIN_70 -to AH[28]
set_location_assignment PIN_41 -to AL[3]
set_location_assignment PIN_40 -to AL[2]
set_location_assignment PIN_39 -to AL[1]
set_location_assignment PIN_37 -to AL[0]
set_location_assignment PIN_48 -to AM[19]
set_location_assignment PIN_46 -to AM[18]
set_location_assignment PIN_45 -to AM[17]
set_location_assignment PIN_44 -to AM[16]
set_location_assignment PIN_54 -to AS_n
set_location_assignment PIN_49 -to AVEC_n
set_location_assignment PIN_55 -to BERR_n
set_location_assignment PIN_61 -to CIIN_n
set_location_assignment PIN_83 -to CLK
set_location_assignment PIN_18 -to CS_DUART_n
set_location_assignment PIN_31 -to CS_ROM_n
set_location_assignment PIN_34 -to CS_SRAM_n
set_location_assignment PIN_50 -to DSACK0_n
set_location_assignment PIN_51 -to DSACK1_n
set_location_assignment PIN_56 -to DS_n
set_location_assignment PIN_63 -to FC[2]
set_location_assignment PIN_64 -to FC[1]
set_location_assignment PIN_65 -to FC[0]
set_location_assignment PIN_16 -to IACK_DUART_n
set_location_assignment PIN_75 -to IPL_n[2]
set_location_assignment PIN_76 -to IPL_n[1]
set_location_assignment PIN_77 -to IPL_n[0]
set_location_assignment PIN_4 -to RST_n
set_location_assignment PIN_60 -to RW
set_location_assignment PIN_58 -to SIZ0
set_location_assignment PIN_57 -to SIZ1
set_location_assignment PIN_52 -to STERM_n
set_location_assignment PIN_5 -to P5
set_location_assignment PIN_6 -to P6
set_location_assignment PIN_8 -to P8
set_location_assignment PIN_9 -to P9
set_location_assignment PIN_10 -to W5500_INT_n
set_global_assignment -name VERILOG_FILE irq_encoder.v
set_global_assignment -name VERILOG_FILE boot_signal.v
set_global_assignment -name VERILOG_FILE system_controller.v
set_location_assignment PIN_21 -to IRQ_DUART_n
set_location_assignment PIN_20 -to DTACK_DUART_n
set_location_assignment PIN_35 -to CS_FPU_n
set_location_assignment PIN_24 -to IDE_BUF_n
set_location_assignment PIN_33 -to DSACK0_FPU_n
set_location_assignment PIN_36 -to DSACK1_FPU_n
set_location_assignment PIN_25 -to IDE_CS0_n
set_location_assignment PIN_22 -to IDE_CS1_n
set_location_assignment PIN_27 -to IDE_INT
set_location_assignment PIN_28 -to IDE_RDY
set_location_assignment PIN_29 -to IDE_RD_n
set_location_assignment PIN_30 -to IDE_WR_n
set_location_assignment PIN_73 -to CS_DRAM_n
set_location_assignment PIN_74 -to DSACK0_DRAM_n
set_location_assignment PIN_81 -to DSACK1_DRAM_n
set_location_assignment PIN_79 -to EXP_BUF_n
